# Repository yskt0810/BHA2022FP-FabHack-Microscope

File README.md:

# FabHack-Microscope

FabHack-Microscope is my Final Project of BioHack Academy 2022.
See details [here](https://yskt0810.github.io/bha2022/projects/fab-hack-microscope/)

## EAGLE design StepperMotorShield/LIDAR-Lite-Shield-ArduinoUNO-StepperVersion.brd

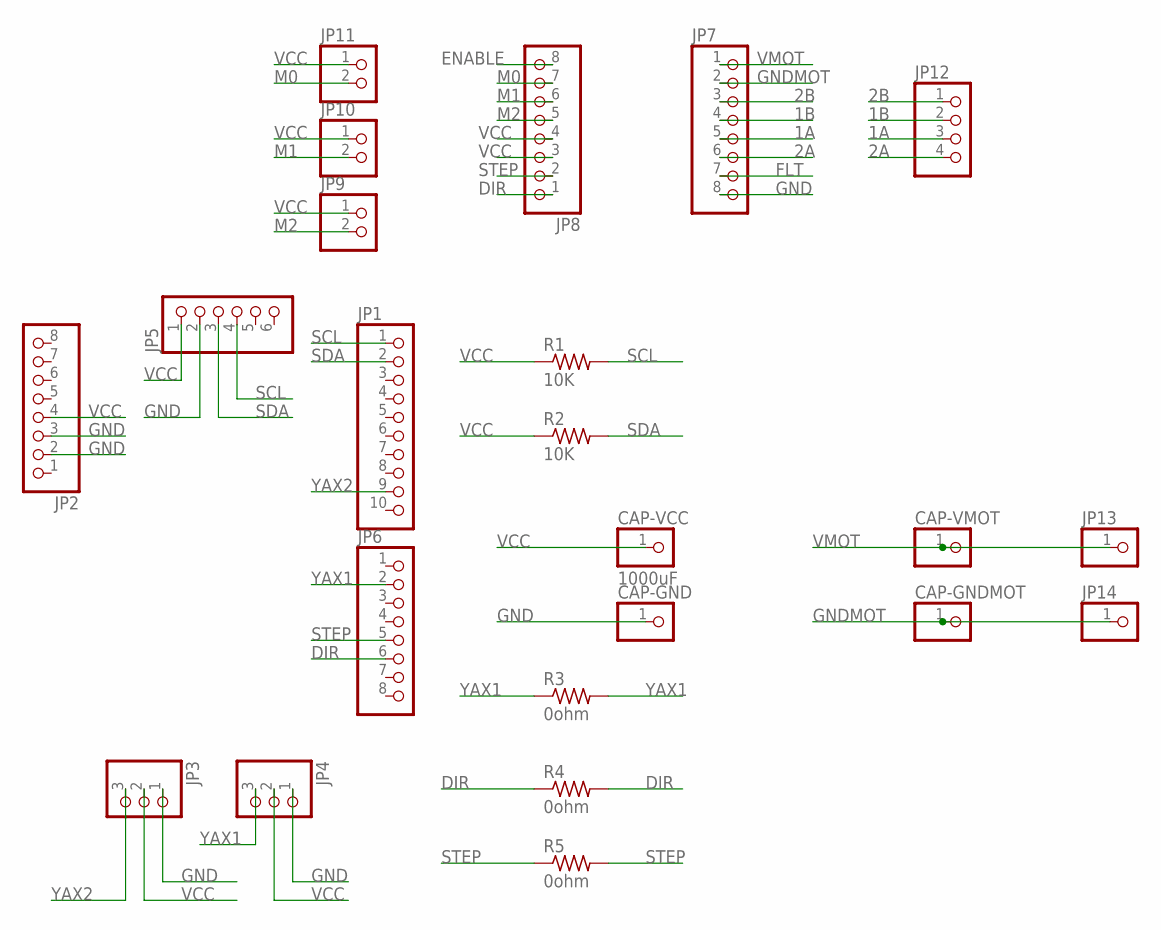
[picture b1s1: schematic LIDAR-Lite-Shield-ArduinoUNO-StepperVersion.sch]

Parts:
CAP-GND: PINHD-1X1; 1X01
CAP-GNDMOT: PINHD-1X1; 1X01
CAP-VCC: 1000uF; 1X01
CAP-VMOT: PINHD-1X1; 1X01
JP1: PINHD-1X10; 1X10
JP2, JP6, JP7, JP8: PINHD-1X8; 1X08
JP3, JP4: PINHD-1X3; 1X03
JP5: PINHD-1X6; 1X06
JP9, JP10, JP11: PINHD-1X2; 1X02
JP12: PINHD-1X4; 1X04
JP13, JP14: PINHD-1X1; 1X01
R1, R2: 10K; R1206FAB
R3, R4, R5: 0ohm; R1206FAB

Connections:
1A: JP7.5, JP12.3
1B: JP7.4, JP12.2
2A: JP7.6, JP12.4
2B: JP7.3, JP12.1
DIR: JP6.6, JP8.1, R4.1, R4.2
ENABLE: JP8.8
FLT: JP7.7
GND: CAP-GND.1, JP2.2, JP2.3, JP3.1, JP4.1, JP5.2, JP7.8
GNDMOT: CAP-GNDMOT.1, JP7.2, JP14.1
M0: JP8.7, JP11.2
M1: JP8.6, JP10.2
M2: JP8.5, JP9.2
SCL: JP1.1, JP5.4, R1.2
SDA: JP1.2, JP5.3, R2.2
STEP: JP6.5, JP8.2, R5.1, R5.2
VCC: CAP-VCC.1, JP2.4, JP3.2, JP4.2, JP5.1, JP8.3, JP8.4, JP9.1, JP10.1, JP11.1, R1.1, R2.1
VMOT: CAP-VMOT.1, JP7.1, JP13.1
YAX1: JP4.3, JP6.2, R3.1, R3.2
YAX2: JP1.9, JP3.3

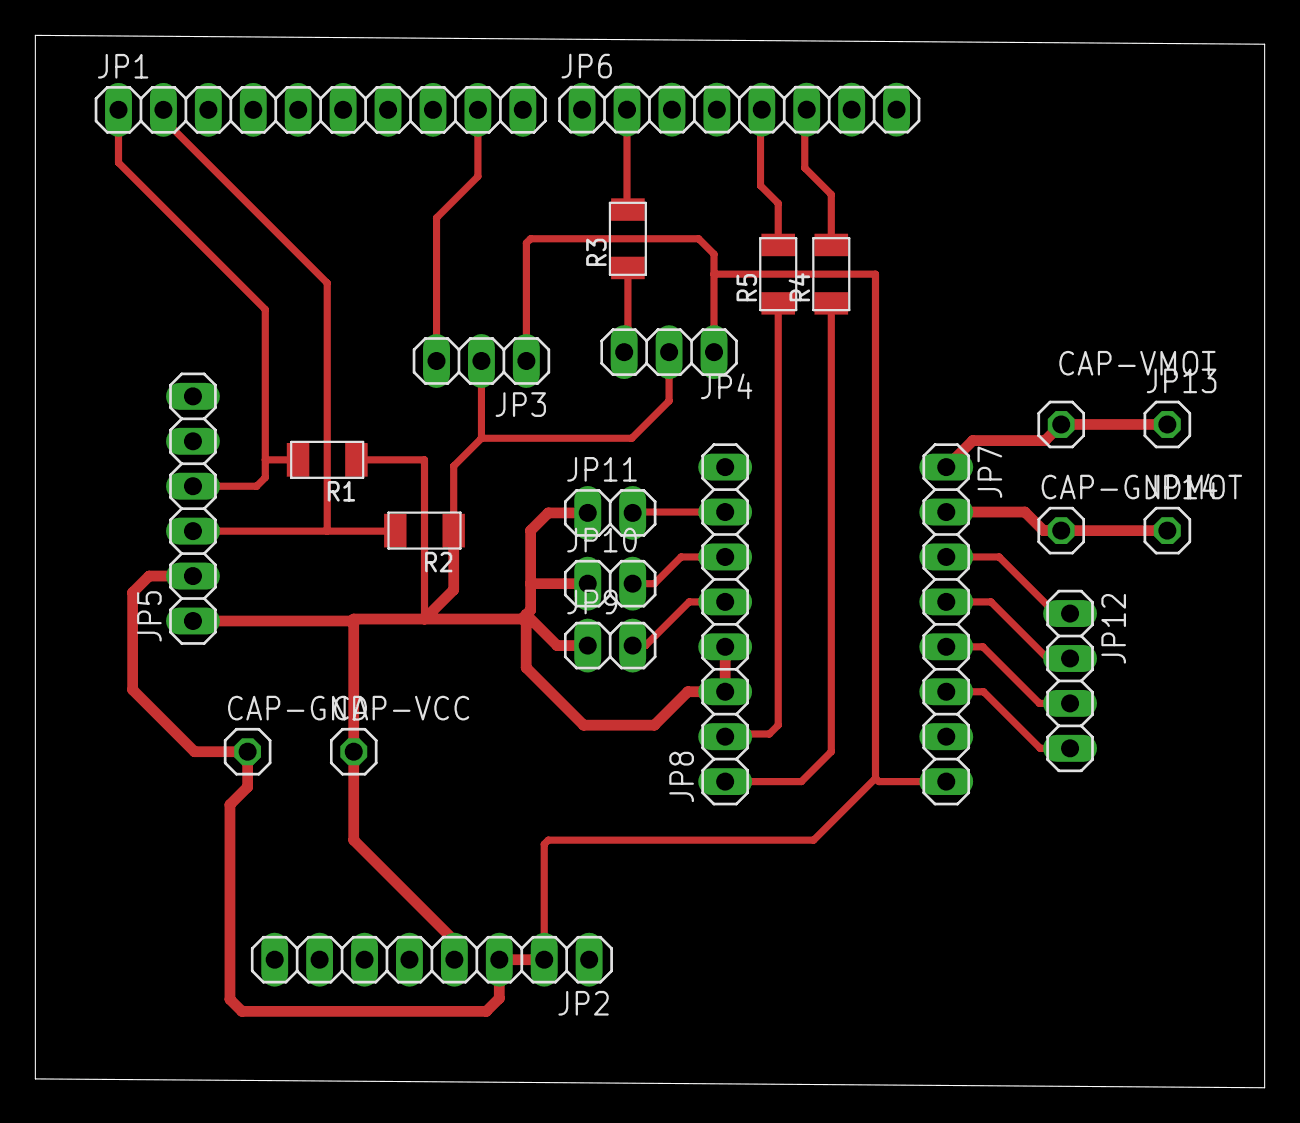
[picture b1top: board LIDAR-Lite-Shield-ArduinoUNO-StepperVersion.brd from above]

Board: 2 copper layers, 69.5 x 59.5 mm, 23 parts (0 on the bottom side), 17 nets.

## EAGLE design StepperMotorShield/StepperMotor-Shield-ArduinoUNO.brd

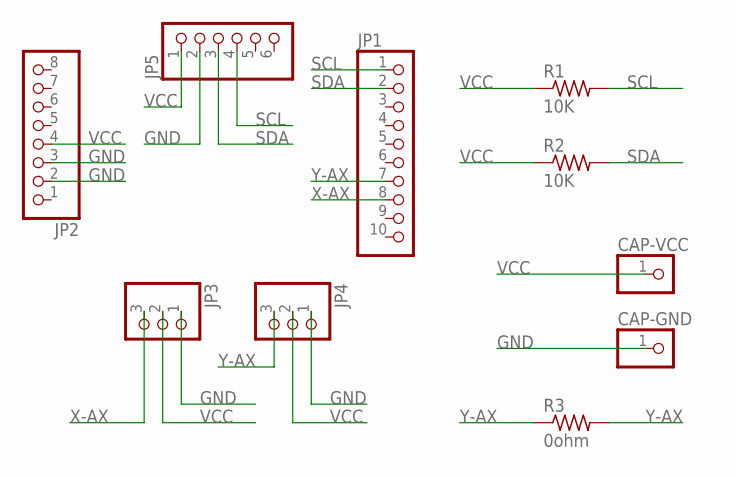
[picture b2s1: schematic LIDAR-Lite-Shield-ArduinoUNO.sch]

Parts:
CAP-GND: PINHD-1X1; 1X01
CAP-VCC: PINHD-1X1; 1X01
JP1: PINHD-1X10; 1X10
JP2: PINHD-1X8; 1X08
JP3, JP4: PINHD-1X3; 1X03
JP5: PINHD-1X6; 1X06
R1, R2: 10K; R1206FAB
R3: 0ohm; R1206FAB

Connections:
GND: CAP-GND.1, JP2.2, JP2.3, JP3.1, JP4.1, JP5.2
SCL: JP1.1, JP5.4, R1.2
SDA: JP1.2, JP5.3, R2.2
VCC: CAP-VCC.1, JP2.4, JP3.2, JP4.2, JP5.1, R1.1, R2.1
X-AX: JP1.8, JP3.3
Y-AX: JP1.7, JP4.3, R3.1, R3.2

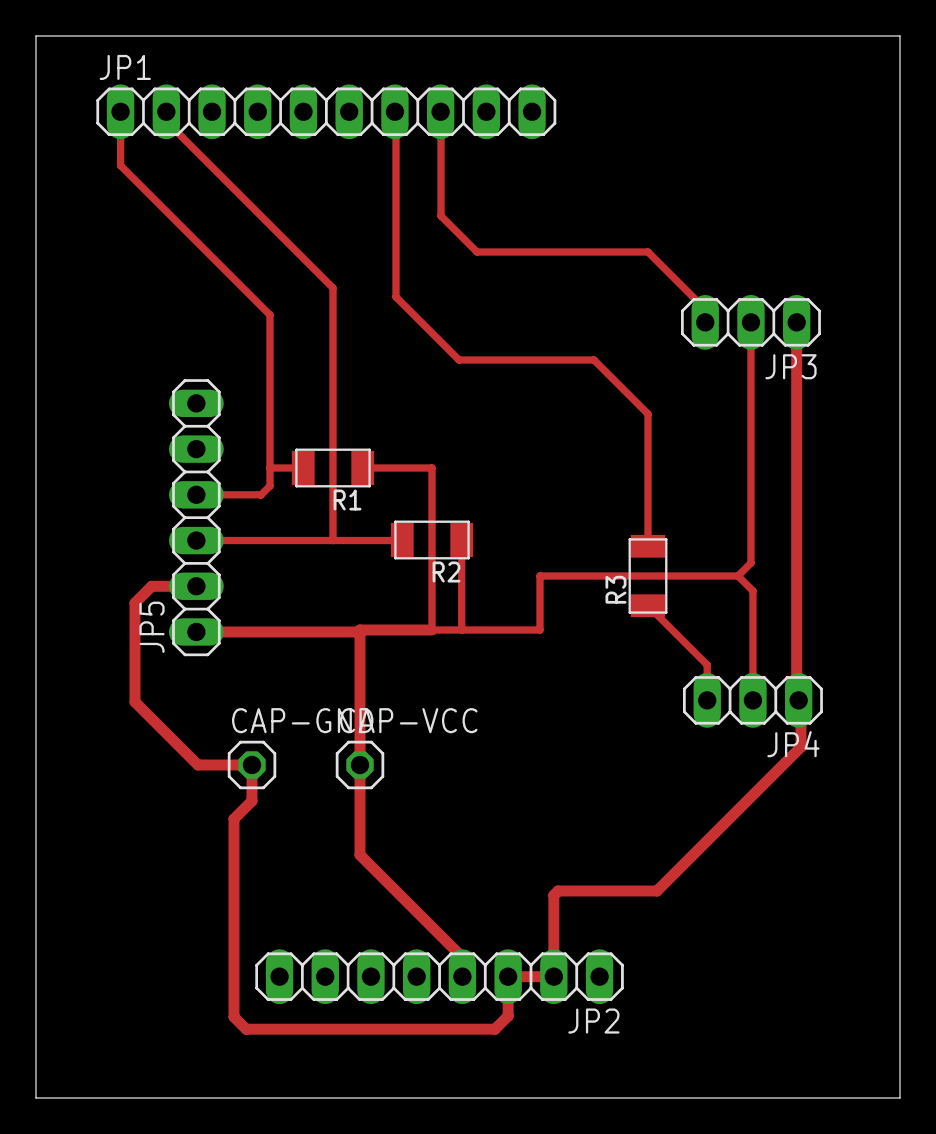
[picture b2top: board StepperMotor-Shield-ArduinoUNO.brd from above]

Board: 2 copper layers, 48.0 x 59.0 mm, 10 parts (0 on the bottom side), 6 nets.

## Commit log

2022-06-02 add eagle files
2022-06-02 change the file name of Eagle files
2022-06-04 add design files
2022-06-04 add microscope body design file
2022-07-25 replace Stepper Motor Shiled PCB Design Files to Correct One
